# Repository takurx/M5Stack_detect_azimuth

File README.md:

# M5Stack_detect_azimuth
It is detecting azimuth on M5Stack + BMM150

# reference
- 9PEO0xNd/M5Gray_MPU6886_BMM150: This is M5Stack Gray MPU6886+BMM150 examples for arduino IDE
  - https://github.com/9PEO0xNd/M5Gray_MPU6886_BMM150
- omegatao/M5StackGrey_MPU6886_BMM150_AHRS_sample: This is a M5Stack grey (MPU6886 + BMM150 version) sample to calculate AHRS status.
  - https://github.com/omegatao/M5StackGrey_MPU6886_BMM150_AHRS_sample

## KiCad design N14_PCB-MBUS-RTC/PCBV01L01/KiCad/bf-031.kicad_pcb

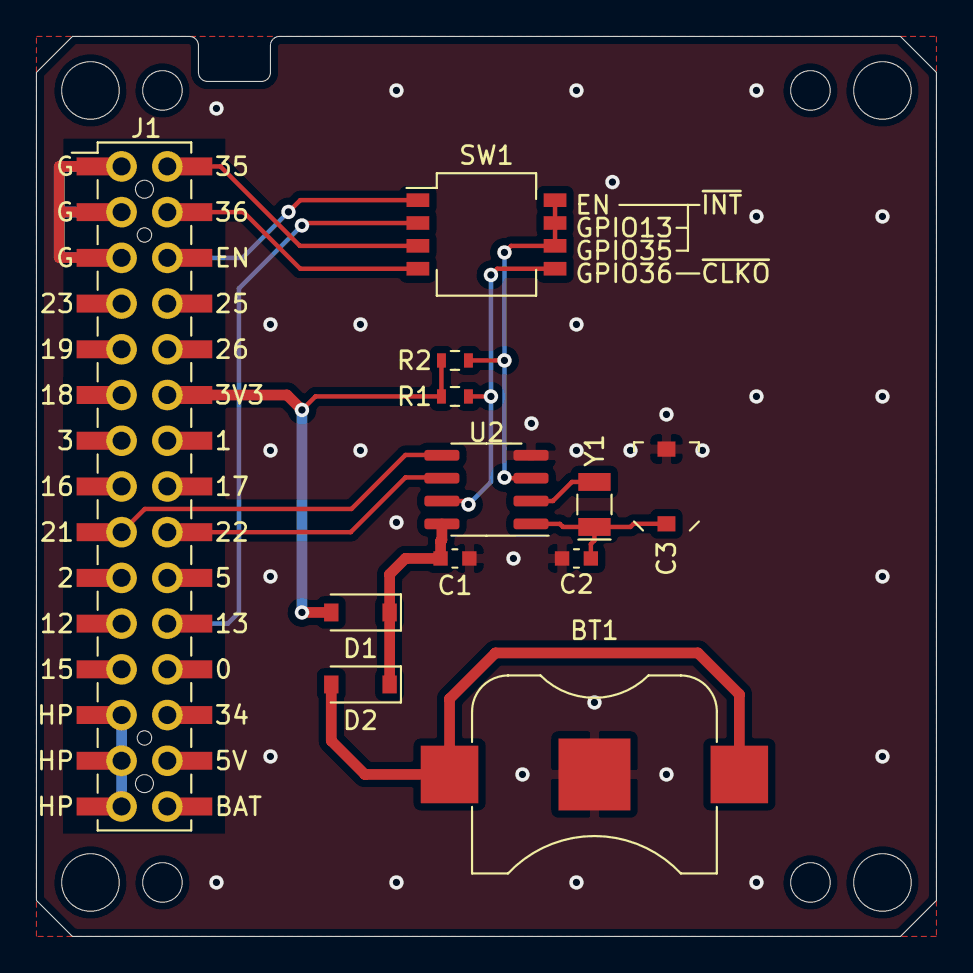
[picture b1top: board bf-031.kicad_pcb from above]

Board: 2 copper layers, 50.0 x 50.0 mm, 20 parts (0 on the bottom side), 15 nets.

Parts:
BT1: CR1220/1225; BF@BatteryHolder_Takachi_SMTM1225
C1: 100n; BF@C_0603_1608Metric
C2: 15p; BF@C_0603_1608Metric
C3: 30p; C_Trimmer_Murata_TZC3
D1, D2: 1N4148; BF@D_SOD-123
H1, H2, H3, H4: MountingHole; BF@MountingHole_3.2mm_M3
H5, H6, H7, H8: MountingHole; BF@MountingHole_2.2mm_M2
J1: M-BUS; BF@M5Stack_MBUS
R1, R2: 10k; BF@R_0603_1608Metric
SW1: SW_DIP_x04; BF@SW_DIP_SPSTx04_Slide_XKB_DSHP04TS-S_W7.62mm_P1.27mm
U2: PCF8563T; SOIC-8_3.9x4.9mm_P1.27mm
Y1: 32768Hz; Crystal_SMD_MicroCrystal_CC7V-T1A-2Pin_3.2x1.5mm

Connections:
+3V3: D1.2, J1.11, R1.1, R2.1
/CLKO: R1.2, SW1.5, U2.7
/EN: J1.5, SW1.1
/GPIO13: J1.21, SW1.2
/GPIO21: J1.18, U2.5
/GPIO22: J1.17, U2.6
/GPIO35: J1.1, SW1.3
/GPIO36: J1.3, SW1.4
/INT: R2.2, SW1.6, SW1.7, SW1.8, U2.3
GND: BT1.2, C1.2, C2.2, C3.2, J1.2, J1.4, J1.6, U2.4
unnamed: BT1.1, D2.2
unnamed: C1.1, D1.1, D2.1, U2.8
unnamed: C2.1, C3.1, U2.1, Y1.1
unnamed: U2.2, Y1.2
VBUS: J1.26, J1.28, J1.30

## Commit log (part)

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2023-06-18 add new project, platformio
    add new project, platformio
2023-06-18 add upload target, /dev/ttyACM0
    add upload target, /dev/ttyACM0
2023-06-18 add Hello, world, lib_deps, m5stack
    add Hello, world, lib_deps, m5stack
2023-06-18 add reference
    add reference
2023-07-08 add test new project, m5stack core s3, platform io
    add test new project, m5stack core s3, platform io
2023-07-08 add python script
    add python script
2023-08-06 add sun azimuth every 5 minutes
    add sun azimuth every 5 minutes
2023-09-17 test display jpg from sd card
    test display jpg from sd card
2023-09-17 test astroplan
    test astroplan
2023-09-17 test tfcard, sdcard
    test tfcard, sdcard
2023-09-17 test cores3, RTCf
    test cores3, RTCf
2023-09-17 test astroplan-1
    test astroplan-1
2023-09-17 test core s3, hello world
    test core s3, hello world
2023-09-17 add install pyenv, error
    add install pyenv, error
2023-09-30 add 1 year sun azimuth and altitude
    add 1 year sun azimuth and altitude
2023-10-08 move folder
    move folder
2023-10-08 add m5stack pin 5 on/off
    add m5stack pin 5 on, button a/off, button b
2023-10-08 add reference
    - 9PEO0xNd/M5Gray_MPU6886_BMM150: This is M5Stack Gray MPU6886+BMM150 examples for arduino IDE
    https://github.com/9PEO0xNd/M5Gray_MPU6886_BMM150
    - omegatao/M5StackGrey_MPU6886_BMM150_AHRS_sample: This is a M5Stack grey (MPU6886 + BMM150 version) sample to calculate AHRS status.
    https://github.com/omegatao/M5StackGrey_MPU6886_BMM150_AHRS_sample
2023-11-19 add read sd card
    add read sd card
2023-11-19 Read 1 line every 1 second.
    Read 1 line every 1 second.
2023-11-19 add M5Stack serial
    add M5Stack serial
2023-11-20 add csv parser
    add csv parser
2023-11-20 add parse from my line
    add parse from my line
2023-11-25 add test date time
    add test date time
2023-11-25 fail, try PCF8563, code for HYM8563/M5Unit-RTC
    fail, try PCF8563, code for HYM8563/M5Unit-RTC
2023-11-25 add sample code
    botanicfields/PCB-MBUS-RTC: PCF8563 RTC Module for M-Bus of M5Stack Basic and Gray
    https://github.com/botanicfields/PCB-MBUS-RTC
2023-11-25 rename data_time -> rtc_data_time
    rename data_time -> rtc_data_time
2023-11-25 add copy for sd card
    add copy for sd card
2023-11-25 add read 1 line every 3 second from sd card
    add read 1 line every 3 second from sd card
2023-11-25 add read from sd card and parse
    add read from sd card and parse
2023-11-25 add rtc + sd card + parse
    add rtc + sd card + parse
2023-11-25 test unixtime
    test unixtime
2023-11-25 ok, convert unixtime
    ok, convert unixtime
2023-11-26 add platformio.ini, fit environment
    add platformio.ini, fit environment
2023-11-29 add combining bmm150
    add combining bmm150
2023-11-29 add combining b on c off
    add combining b on c off
2023-11-30 ok, working compass
    ok, working compass
2023-11-30 ok, b on and c off
    ok, b on and c off
2023-11-30 add tracking, Work In Progress
    add tracking, Work In Progress
2023-11-30 add tracking algorithm, work in progress
    add tracking algorithm, work in progress
2023-11-30 traking plan1
    traking plan1
2023-11-30 sd card data, seek fail, stack smashing protect failure
    sd card data, seek fail, stack smashing protect failure
2023-11-30 update tracking plan1 and error stack smashing after read 2-3 days
    update tracking plan1 and error stack smashing after read 2-3 days
2023-11-30 ok, seek
    ok, seek
2023-12-05 add test common str
    add test common str
2024-02-11 add test pwm
    add test pwm
2024-02-12 add button abc
    add button abc
2024-03-17 add 5 minutes and seek
    add 5 minutes and seek
2024-03-23 ok 5 minutes
    ok 5 minutes
2024-03-23 csv is UTC, RTC set also UTC
    csv is UTC, RTC set also UTC
2024-03-24 ok const
    ok const
2024-03-24 add rename folder
    add rename folder
2024-03-25 n26, angle決め打ち
    n26, angle決め打ち
2024-04-16 N24, PWM, 0.75 deg (0.5-1.0 deg)
    N24, PWM, 0.75 deg (0.5-1.0 deg)
2024-04-16 N27, 0.9deg, ±0.5deg, Reset button 90.0/180.0/0.0
    N27, 0.9deg, ±0.5deg, Reset button 90.0/180.0/0.0
2024-04-18 add N28
    add N28
2024-04-18 N28, add run/stop button
    N28, add run/stop button
2024-04-18 N28, fix 360->0 when mid night, boundary value
    N28, fix 360->0 when mid night, boundary value
2024-04-18 N28, initial, target azimuth, 回転持続
    N28, initial, target azimuth, 回転持続
2024-04-21 N28, add Osaka
    N28, add Osaka
2024-04-30 add trying bno055
    add trying bno055
2024-05-06 WIP, test TinyGPSPlus fail
    WIP, test TinyGPSPlus fail
2024-07-14 add N32, gps from uart
    add N32, gps from uart
2024-10-27 add N33, refactoring
    add N33, refactoring
2024-11-27 add N33, refactoring 2
    add N33, refactoring 2
2024-11-27 add WIP N34 BNO055 <- MPU6886+BMM150
    add WIP N34 BNO055 <- MPU6886+BMM150
2024-11-28 add BNO055 code to N34 WIP
    add BNO055 code to N34 WIP
2024-12-01 add N29, M5.Lcd
    add N29, M5.Lcd
2024-12-01 add csv, osaka
    add csv, osaka
2024-12-02 add N34 replace BNO055
    add N34 replace BNO055
2024-12-02 N34, 360->0.0の境界時の条件を調整
    N34, 360->0.0の境界時の条件を調整
2024-12-02 N34, BNO055 system=3, mag>=2のとき、sensorの値を信用する
    N34, BNO055 system=3, mag>=2のとき、sensorの値を信用する
2024-12-02 N34, AUTOではなくSENSORモードと名称変更
    N34, AUTOではなくSENSORモードと名称変更
2025-01-19 add WIP N35 button ABC, M5stack
    add WIP N35 button ABC, M5stack
2025-01-19 N35, Button ABC push
    N35, Button ABC push
2025-01-19 N35, push and display state on LCD and Serial
    N35, push and display state on LCD and Serial
2026-01-01 add 260101
    add 260101

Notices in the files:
N14_PCB-MBUS-RTC/PCBV01L01/KiCad/bf-031.kicad_pcb:
Copyright 2021 BotanicFields, Inc.
